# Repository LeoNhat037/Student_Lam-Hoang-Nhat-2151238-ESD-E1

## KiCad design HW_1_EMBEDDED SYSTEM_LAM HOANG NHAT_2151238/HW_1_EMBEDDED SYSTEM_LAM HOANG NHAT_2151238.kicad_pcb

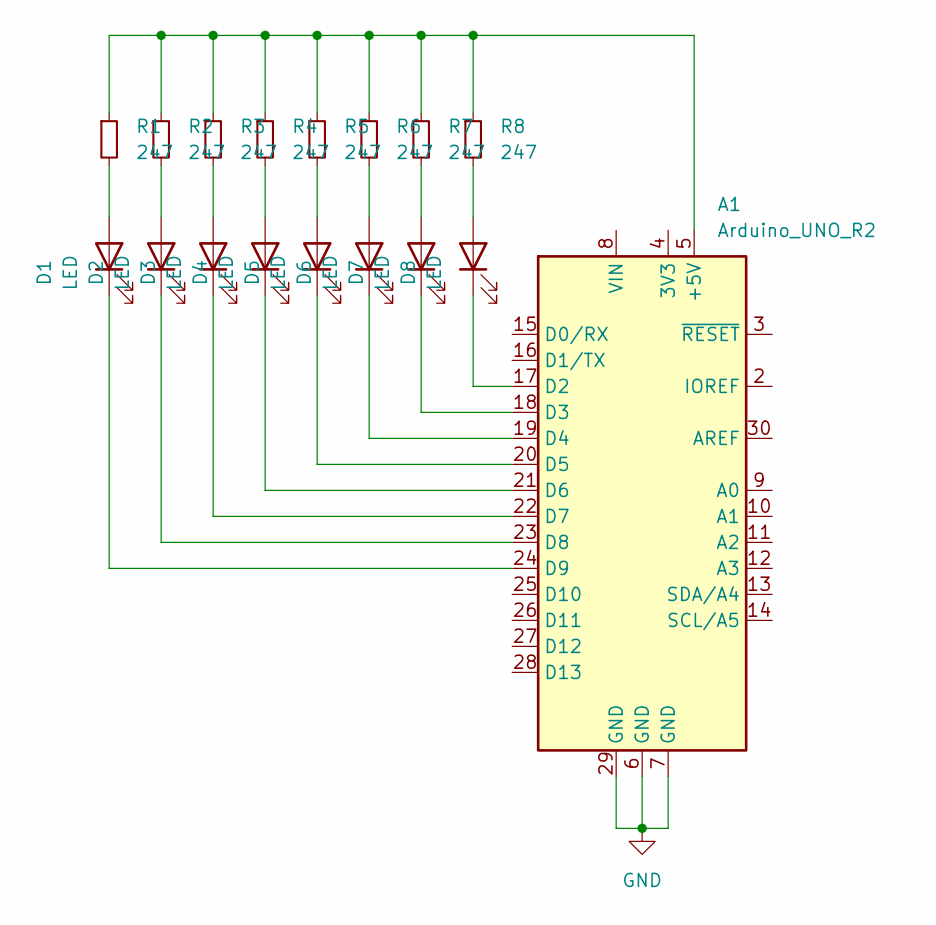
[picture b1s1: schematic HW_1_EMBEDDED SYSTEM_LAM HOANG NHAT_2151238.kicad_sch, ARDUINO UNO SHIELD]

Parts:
A1: Arduino_UNO_R2
D1, D2, D3, D4, D5, D6, D7, D8: LED; LED_0805_2012Metric_Pad1.15x1.40mm_HandSolder
R1, R2, R3, R4, R5, R6, R7, R8: 247; R_0603_1608Metric

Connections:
GND: A1.6 (GND), A1.7 (GND), A1.29 (GND)
unnamed: A1.5 (+5V), R1.1, R2.1, R3.1, R4.1, R5.1, R6.1, R7.1, R8.1
unnamed: A1.17 (D2), D8.1 (K)
unnamed: A1.18 (D3), D7.1 (K)
unnamed: A1.19 (D4), D6.1 (K)
unnamed: A1.20 (D5), D5.1 (K)
unnamed: A1.21 (D6), D4.1 (K)
unnamed: A1.22 (D7), D3.1 (K)
unnamed: A1.23 (D8), D2.1 (K)
unnamed: A1.24 (D9), D1.1 (K)
unnamed: D1.2 (A), R1.2
unnamed: D2.2 (A), R2.2
unnamed: D3.2 (A), R3.2
unnamed: D4.2 (A), R4.2
unnamed: D5.2 (A), R5.2
unnamed: D6.2 (A), R6.2
unnamed: D7.2 (A), R7.2
unnamed: D8.2 (A), R8.2

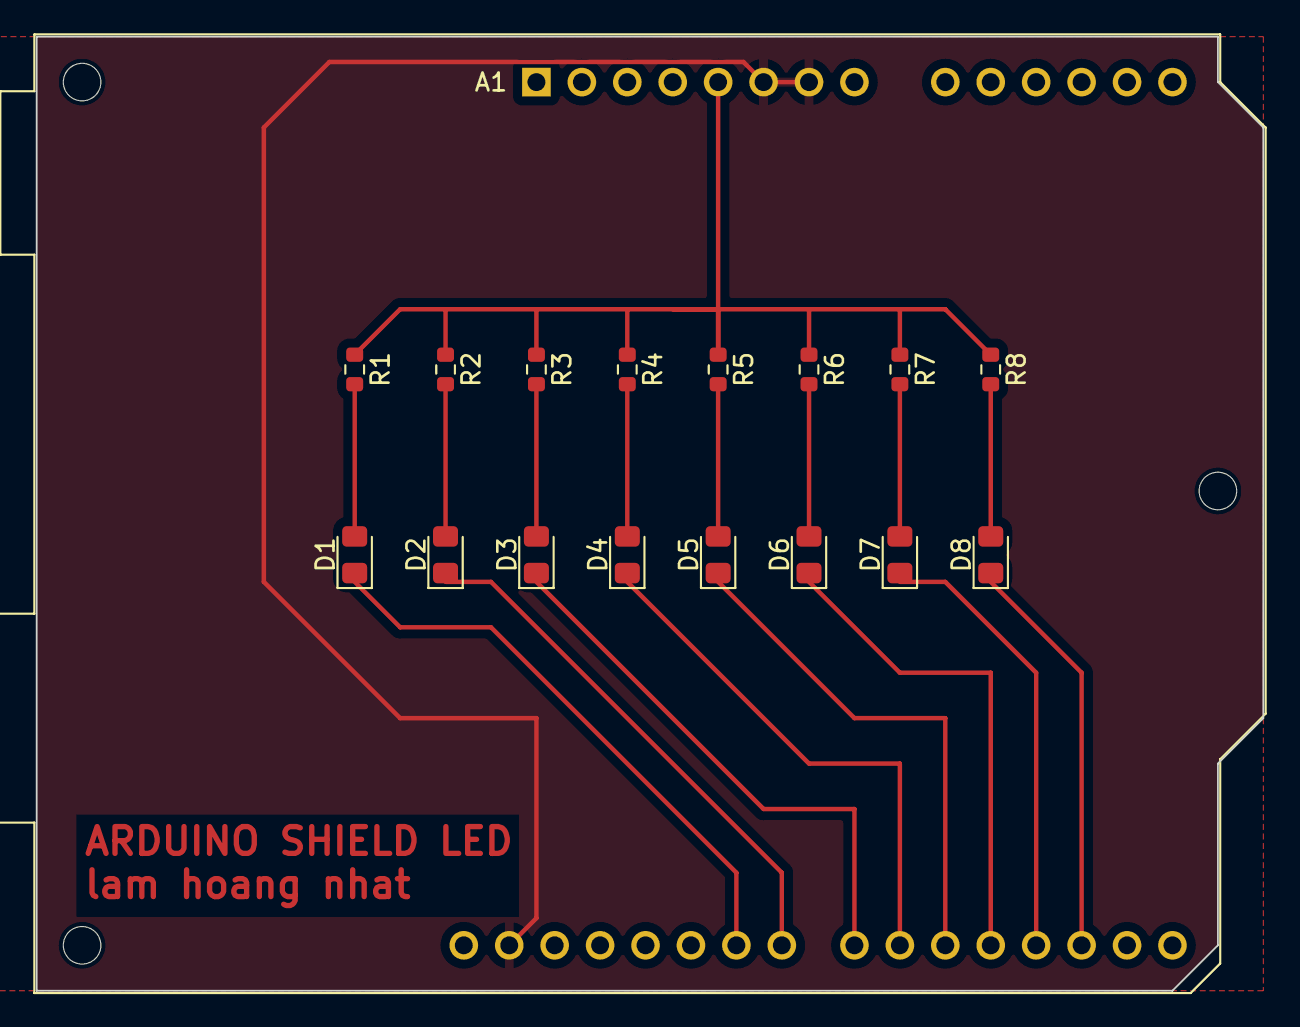
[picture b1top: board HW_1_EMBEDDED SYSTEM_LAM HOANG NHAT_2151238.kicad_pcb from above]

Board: 2 copper layers, 68.6 x 53.3 mm, 17 parts (0 on the bottom side), 18 nets.

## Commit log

2024-01-14 Create home_work_1
